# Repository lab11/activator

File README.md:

activator
=========

Hardware that can be used with an energy-harvesting power supply to do sensing.

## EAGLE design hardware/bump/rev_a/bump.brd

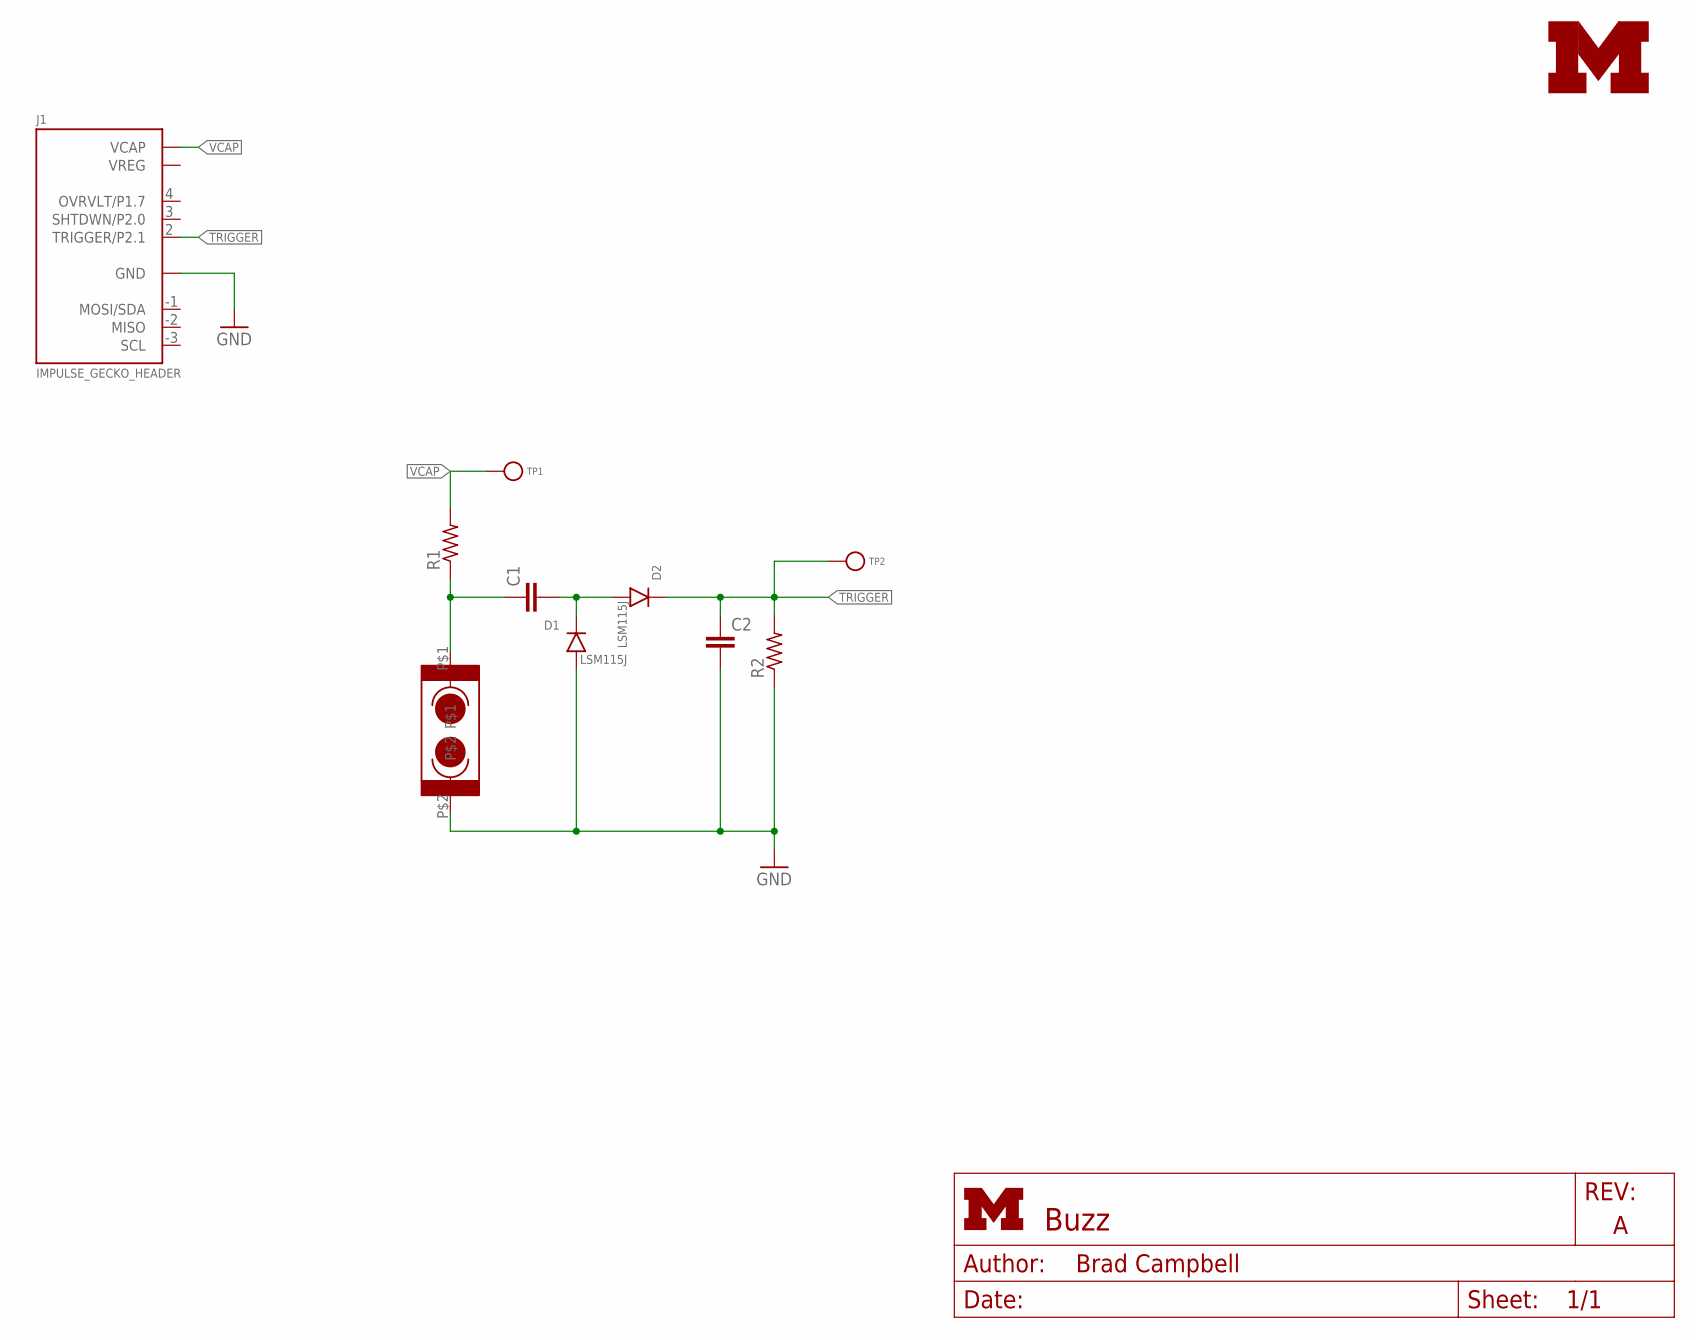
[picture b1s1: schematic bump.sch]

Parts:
C1, C2: C-EUC0603; C0603
D1, D2: LSM115J; D0-214BA
J1: IMPULSE_GECKO_HEADER; HEADER1X9/0.05IN
R1, R2: R-US_R0603; R0603
TP1, TP2: TEST_POINT_0.040IN; TESTPOINT_0.040IN
U$3: UMICH_SOLID_SMALL+; UMICH_SOLID_100MIL
VS1: SQ-SEN-200

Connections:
GND: C2.2, D1.A, J1.0 (GND), R2.1, VS1.P$2
unnamed: C1.1, R1.1, VS1.P$1
unnamed: C1.2, D1.C, D2.A
TRIGGER: C2.1, D2.C, J1.2 (TRIGGER/P2.1), R2.2, TP2.TESTPOINT
VCAP: J1.5 (VCAP), R1.2, TP1.TESTPOINT

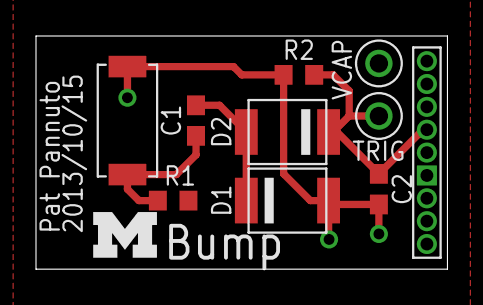
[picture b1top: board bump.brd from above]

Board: 2 copper layers, 22.9 x 13.0 mm, 11 parts (0 on the bottom side), 5 nets.

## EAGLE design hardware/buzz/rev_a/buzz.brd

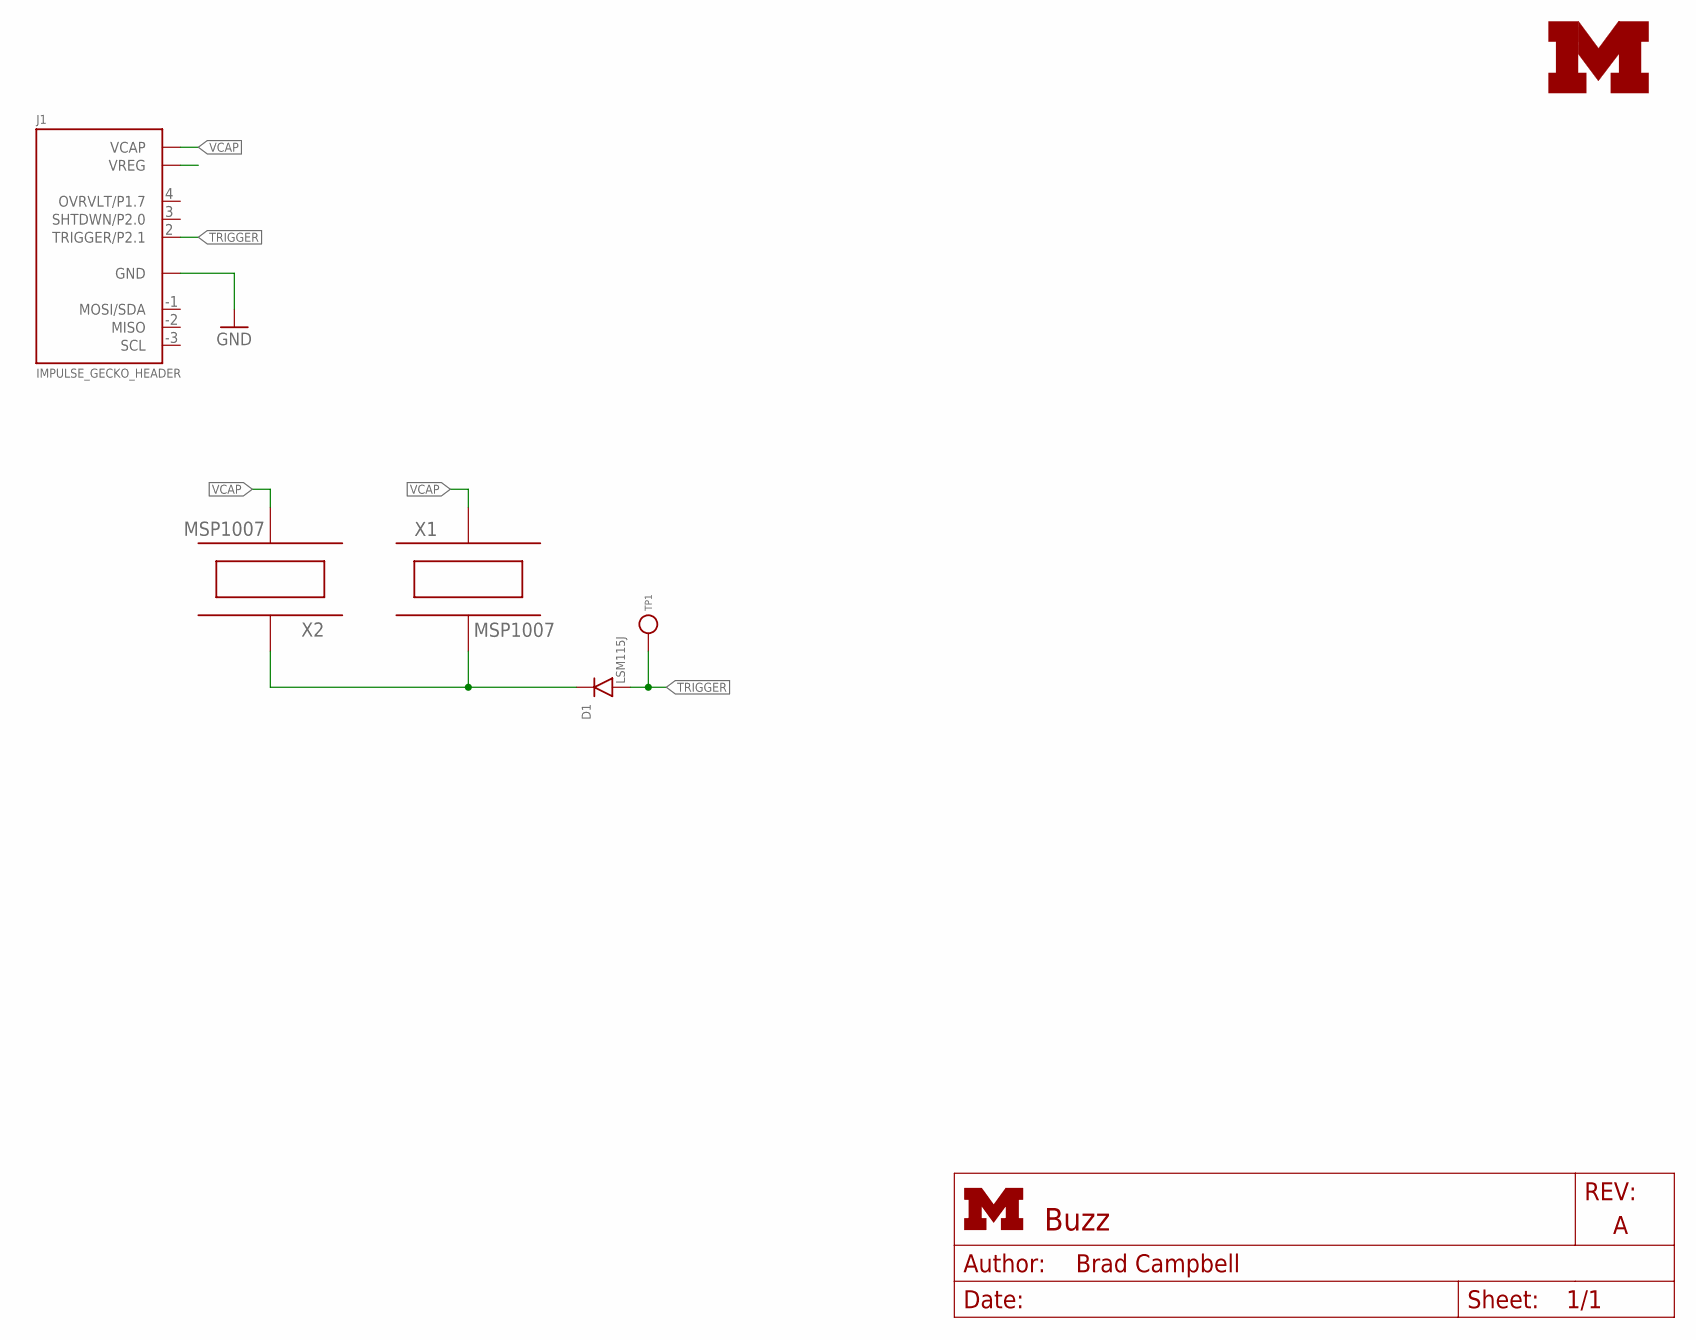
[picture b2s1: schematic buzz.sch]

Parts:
D1: LSM115J; D0-214BA
J1: IMPULSE_GECKO_HEADER; HEADER1X9/0.05IN
TP1: TEST_POINT_0.040IN; TESTPOINT_0.040IN
U$3: UMICH_SOLID_SMALL+; UMICH_SOLID_100MIL
X1, X2: MSP1007

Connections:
GND: J1.0 (GND)
unnamed: D1.C, X1.2, X2.1
TRIGGER: D1.A, J1.2 (TRIGGER/P2.1), TP1.TESTPOINT
VCAP: J1.5 (VCAP), X1.1, X2.2

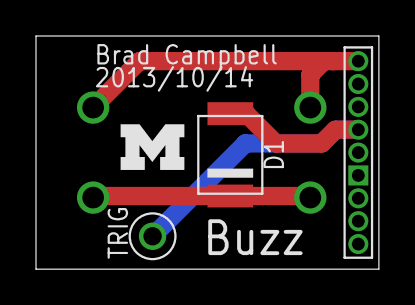
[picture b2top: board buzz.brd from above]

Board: 2 copper layers, 19.1 x 13.0 mm, 6 parts (0 on the bottom side), 3 nets.

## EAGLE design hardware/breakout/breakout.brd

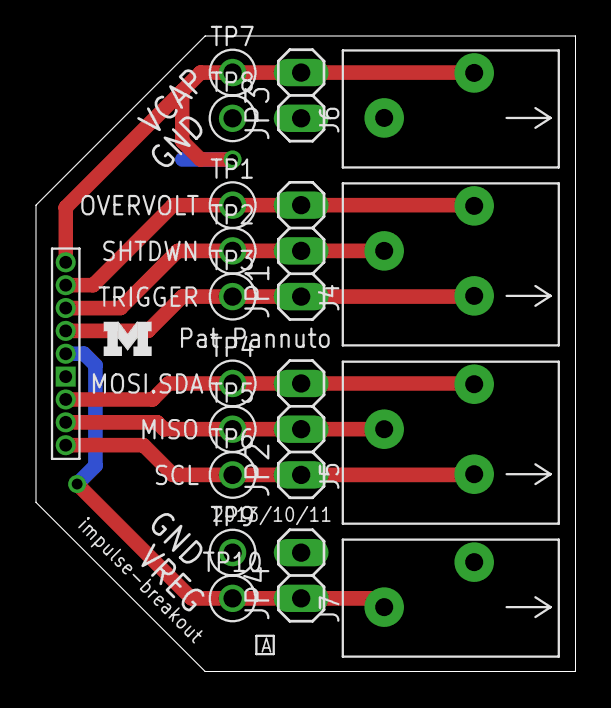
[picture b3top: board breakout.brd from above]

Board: 2 copper layers, 30.0 x 35.3 mm, 20 parts (0 on the bottom side), 9 nets.

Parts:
J3: IMPULSE_GECKO_HEADER; HEADER1X9/0.05IN
J4, J5: SPRING-TERMINAL_3/PTSA-ZZ_2.5MM; 1X3/PTSA-ZZ_2.5MM
J6, J7: SPRING-TERMINAL_2/PTSA-ZZ_2.5MM; 1X2/PTSA-ZZ_2.5MM
JP1, JP2: 1X03
JP3, JP4: 1X02
TP1, TP2, TP3, TP4, TP5, TP6, TP7, TP8, TP9, TP10: TEST_POINT_0.040IN; TESTPOINT_0.040IN
U$1: UMICH_SOLID_SMALL; UMICH_SOLID_75MIL

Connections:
GND: J3.0, J6.1, J7.2, JP3.1, JP4.2, TP8.TESTPOINT, TP9.TESTPOINT
MISO0: J3.-2, J5.2, JP2.2, TP5.TESTPOINT
MOSI0: J3.-1, J5.3, JP2.3, TP4.TESTPOINT
OV: J3.4, J4.3, JP1.3, TP1.TESTPOINT
SCLK0: J3.-3, J5.1, JP2.1, TP6.TESTPOINT
SHD: J3.3, J4.2, JP1.2, TP2.TESTPOINT
TRIG: J3.2, J4.1, JP1.1, TP3.TESTPOINT
VCAP: J3.5, J6.2, JP3.2, TP7.TESTPOINT
VCC: J3.1, J7.1, JP4.1, TP10.TESTPOINT

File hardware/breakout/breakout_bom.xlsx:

Qty | Value | Device | Package | Parts | Description | DIGIKEY
2 |  | PINHD-1X2 | 1X02 | JP3, JP4 | PIN HEADER
2 |  | PINHD-1X3 | 1X03 | JP1, JP2 | PIN HEADER
1 | IMPULSE_GECKO_HEADER | IMPULSE_GECKO_HEADER | HEADER1X9/0.05IN | J3 | Header on the impulse EPIC-esque board.
2 | SPRING-TERMINAL_2/PTSA-ZZ_2.5MM | SPRING-TERMINAL_2/PTSA-ZZ_2.5MM | 1X2/PTSA-ZZ_2.5MM | J6, J7 |  | 277-1794-ND
2 | SPRING-TERMINAL_3/PTSA-ZZ_2.5MM | SPRING-TERMINAL_3/PTSA-ZZ_2.5MM | 1X3/PTSA-ZZ_2.5MM | J4, J5 |  | 277-1795-ND
10 | TEST_POINT_0.040IN | TEST_POINT_0.040IN | TESTPOINT_0.040IN | TP1, TP2, TP3, TP4, TP5, TP6, TP7, TP8, TP9, TP10 | 0.040in Test Point | 5001K-ND

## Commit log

2013-10-11 buzz board piezo
2013-10-11 added a script to generate qr codes
2013-10-11 gitignore
2013-10-11 better gitignore
2013-10-11 bom for buzz
2013-10-11 removed print statement
2013-10-11 Add PIR stub for future
2013-10-11 Add breakout board
2013-10-15 updates to boards
2013-10-15 Add vibration board
2013-10-16 tent vias, name rev_a
2013-10-16 Add boardhouse files
2013-10-28 moved impulse to activator repo
2013-10-28 moved sEHnsor to activator repo
2013-10-28 added breakout board bom
2013-10-28 moved contiki from gecko to activator
2013-10-28 impulse rev c ready to ship
2013-10-28 updated bom with digireel
    impulse rev c
2013-10-28 added logo .ai file
2013-10-28 updated qr code script i guess
2013-12-14 removed boards that moved to monjolo
2013-12-14 removed qr code script
2013-12-14 contiki moved to monjolo
2013-12-14 no software
2014-01-09 Move bom to correct folder
2014-01-09 Update info entry for this board to add description
2014-01-09 Update info to add description
2014-01-09 Add description, fix project name in schematic attribute
2014-01-09 Add github links to info files
2014-01-09 Update author attribute
2014-01-10 Add picture of built breakout board
2014-01-14 buzz rev a doc
2014-01-14 new buzz pic
2014-05-26 Add B-Switch (Reed Switch) board
